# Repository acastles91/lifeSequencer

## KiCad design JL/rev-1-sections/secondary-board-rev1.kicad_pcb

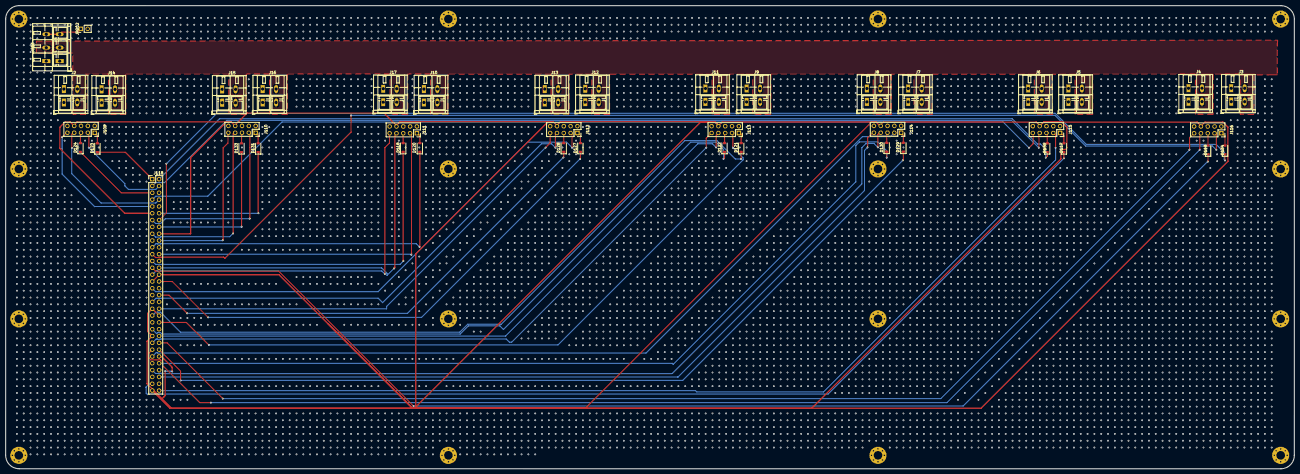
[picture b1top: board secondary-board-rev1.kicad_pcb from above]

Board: 4 copper layers, 480.0 x 172.5 mm, 59 parts (0 on the bottom side), 61 nets.

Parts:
D117, D118, D119, D120, D121, D122, D123, D124, D127, D128, D129, D130, D131, D132, D133, D134: D; D_SOD-123
H108, H108#2, H108#3, H108#4, H108#5, H108#6, H108#7, H108#8, H108#9, H108#10, H108#11, H108#12, H108#13, H108#14, H108#15, H108#16: MountingHole; MountingHole_3.2mm_M3_Pad_Via
J2, J3, J4, J5, J6, J7, J8, J9, J10, J11, J12, J13, J14, J15, J16, J17: Screw_Terminal_01x02; TerminalBlock_WAGO_236-402_1x02_P5.00mm_45Degree
J109, J110, J111, J112, J113, J114, J115, J116: Conn_01x10; PinSocket_2x05_P2.54mm_Vertical
J118: Conn_02x32_Odd_Even; PinHeader_2x32_P2.54mm_Vertical
J203: Screw_Terminal_01x03; TerminalBlock_WAGO_236-403_1x03_P5.00mm_45Degree
JP202: Jumper_2_Open; PinHeader_1x02_P2.54mm_Vertical

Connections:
CV_8: J109.9, J118.9
CV_9: J110.9, J118.20
CV_10: J111.9, J118.29
CV_11: J112.9, J118.40
CV_12: J113.9, J118.49
CV_13: J114.9, J118.60
CV_14: J115.9, J118.7
CV_15: J116.9, J118.50
CV_OUTPUT_8: D124.2 (A), J109.5
CV_OUTPUT_9: D133.2 (A), J110.5
CV_OUTPUT_10: D118.2 (A), J111.5
CV_OUTPUT_11: D128.2 (A), J112.5
CV_OUTPUT_12: D122.2 (A), J113.5
CV_OUTPUT_13: D130.2 (A), J114.5
CV_OUTPUT_14: D132.2 (A), J115.5
CV_OUTPUT_15: D119.2 (A), J116.5
EARTH-2: J203.3, JP202.1 (A)
GATE_8: J109.3, J118.4
GATE_9: J110.3, J118.13
GATE_10: J111.3, J118.24
GATE_11: J112.3, J118.33
GATE_12: J113.3, J118.44
GATE_13: J114.3, J118.53
GATE_14: J115.3, J118.64
GATE_15: J116.3, J118.23
GATE_OUTPUT_8: D123.2 (A), J109.1
GATE_OUTPUT_9: D131.2 (A), J110.1
GATE_OUTPUT_10: D120.2 (A), J111.1
GATE_OUTPUT_11: D127.2 (A), J112.1
GATE_OUTPUT_12: D121.2 (A), J113.1
GATE_OUTPUT_13: D129.2 (A), J114.1
GATE_OUTPUT_14: D117.2 (A), J115.1
GATE_OUTPUT_15: D134.2 (A), J116.1
LINE2: J2.2, J3.2, J4.2, J5.2, J6.2, J7.2, J8.2, J9.2, J10.2, J11.2, J12.2, J13.2, J14.2, J15.2, J16.2, J17.2, J203.2
NEUT2: J2.1, J3.1, J4.1, J5.1, J6.1, J7.1, J8.1, J9.1, J10.1, J11.1, J12.1, J13.1, J14.1, J15.1, J16.1, J17.1, J203.1
unnamed: D117.1 (K), J118.61
unnamed: D118.1 (K), J118.25
unnamed: D119.1 (K), J118.27
unnamed: D120.1 (K), J118.21
unnamed: D121.1 (K), J118.41
unnamed: D122.1 (K), J118.45
unnamed: D123.1 (K), J118.1
unnamed: D124.1 (K), J118.5
unnamed: D127.1 (K), J118.32
unnamed: D128.1 (K), J118.36
unnamed: D129.1 (K), J118.52
unnamed: D130.1 (K), J118.56
unnamed: D131.1 (K), J118.12
unnamed: D132.1 (K), J118.2
unnamed: D133.1 (K), J118.16
unnamed: D134.1 (K), J118.14
RELAYS_8: J109.7, J118.8
RELAYS_9: J110.7, J118.17
RELAYS_10: J111.7, J118.28
RELAYS_11: J112.7, J118.37
RELAYS_12: J113.7, J118.48
RELAYS_13: J114.7, J118.57
RELAYS_14: J115.7, J118.3
RELAYS_15: J116.7, J118.51
SECONDARY_5VA: J109.8, J110.8, J111.8, J112.8, J113.8, J114.8, J115.8, J116.8, J118.11, J118.18, J118.30, J118.31, J118.39, J118.42, J118.47, J118.54, J118.63
SECONDARY_GND: J109.2, J109.4, J109.6, J109.10, J110.2, J110.4, J110.6, J110.10, J111.2, J111.4, J111.6, J111.10, J112.2, J112.4, J112.6, J112.10, J113.2, J113.4, J113.6, J113.10, J114.2, J114.4, J114.6, J114.10, J115.2, J115.4, J115.6, J115.10, J116.2, J116.4, J116.6, J116.10, J118.6, J118.10, J118.15, J118.19, J118.22, J118.26, J118.34, J118.35, J118.38, J118.43, J118.46, J118.55, J118.58, J118.59, J118.62, JP202.2 (B)

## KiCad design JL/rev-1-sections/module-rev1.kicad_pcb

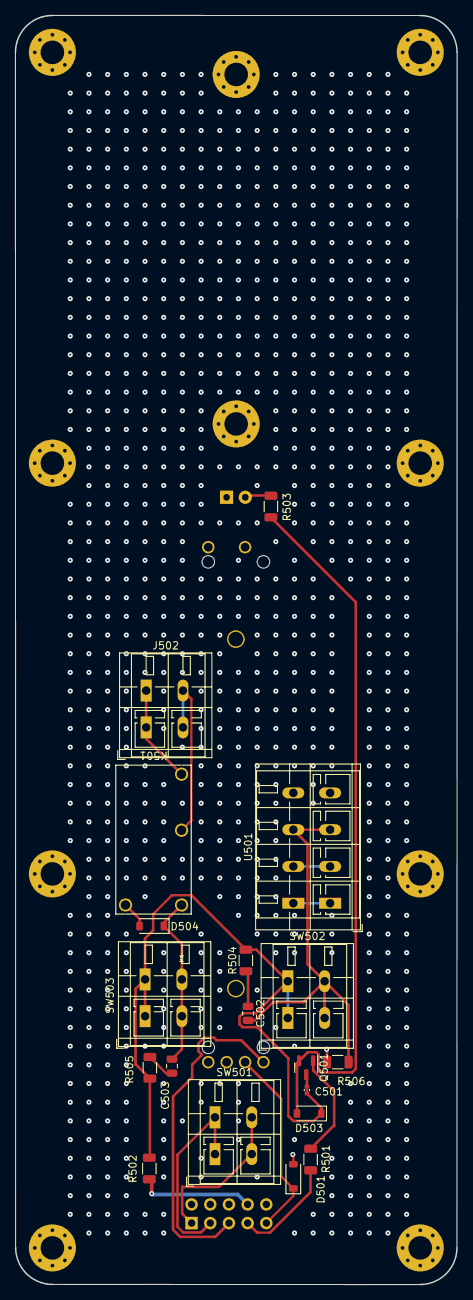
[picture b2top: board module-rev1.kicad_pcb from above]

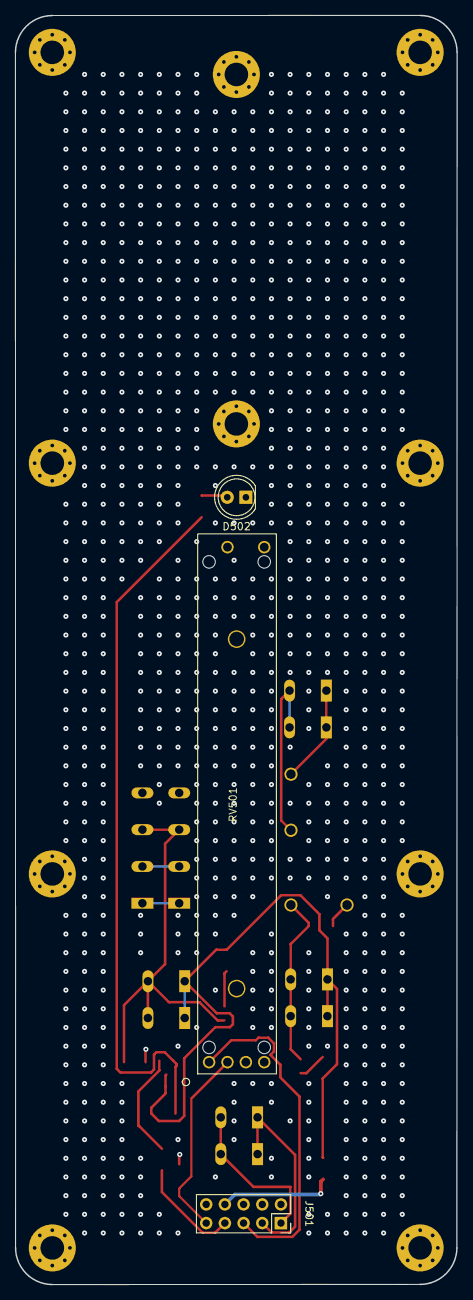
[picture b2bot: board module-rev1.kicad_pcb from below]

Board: 4 copper layers, 60.0 x 172.5 mm, 32 parts (3 on the bottom side), 17 nets.

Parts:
C501: C; C_0402_1005Metric
C502, C503: C; C_0805_2012Metric
D501, D503, D504: D; D_SOD-123
D502: LED; LED_D5.0mm
H108, H108#2, H108#3, H108#4, H108#5, H108#6, H108#7, H108#8, H108#9, H108#10: MountingHole; MountingHole_3.2mm_M3_Pad_Via
J501: Conn_01x10; PinSocket_2x05_P2.54mm_Vertical
J502: Screw_Terminal_01x02; TerminalBlock_WAGO_236-402_1x02_P5.00mm_45Degree
K501: ALQ305; RELAY_ALQ3_PAN
Q501: BC817; SOT-23
R501, R502, R503, R504, R505, R506: R_US; R_1206_3216Metric
RV501: R_Potentiometer_US; POT_SEGOR_10K
SW501: SW_Push; TerminalBlock_WAGO_236-402_1x02_P5.00mm_45Degree
SW502, SW503: SW_SPST; TerminalBlock_WAGO_236-402_1x02_P5.00mm_45Degree
U501: AQ-A_Solid_State_Relay; TerminalBlock_WAGO_236-404_1x04_P5.00mm_45Degree

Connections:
/module-master/A_to_ALQ305_0: C503.2, D504.1 (K), K501.1, SW503.2 (B)
/module-master/E_to_R_0: D503.2 (A), Q501.2 (E), R503.2
/module-master/R_to_B_0: Q501.1 (B), R501.2
/module-master/R_to_C_0: C501.1, C501.2, D503.1 (K), Q501.3 (C), R502.2, R504.2, R505.1, SW502.1 (A), SW503.1 (A)
/module-master/R_to_KLED_0: D502.2 (A), R503.1
/module-master/SHUNT_1_0: C502.1, R504.1
/module-master/SHUNT_2_0: C503.1, R505.2
/module-master/SW_to_AQ-A_IN_0: C502.2, R506.2, SW502.2 (B), U501.3 (In+)
unnamed: J502.1, K501.4
unnamed: J502.2, K501.3
_5VA_0: J501.8, R502.1
_CV_0: D501.1 (K), J501.9, RV501.1
_CV_OUTPUT_0: J501.5, RV501.2
_GATE_0: J501.3, SW501.1
_GATE_OUTPUT_0: J501.1, SW501.2
_GND_0: D501.2 (A), D502.1 (K), D504.2 (A), J501.2, J501.4, J501.6, J501.10, K501.2, R506.1, RV501.3, U501.4 (In-)
_RELAYS_0: J501.7, R501.1

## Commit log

2023-12-02 jlc pcb order
